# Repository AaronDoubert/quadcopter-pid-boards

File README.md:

# Quadcopter Flight Controller – Analog PID Boards

Analog PID flight controller for a 5" quadcopter: roll, pitch and yaw loops built from op-amps and
trimpots, fed by an MPU-6050 through a small ATtiny/DAC "shim", driving a 4in1 ESC. Designed in KiCad 10.

## PID_Board rev B: compact through-hole board for the 5" frame (latest)

**90 x 210 mm, 4-layer, all through-hole except the two SOIC ATtinys.** It mounts straight onto the frame.

| | |
|---|---|
| Mounting | 30.5 x 30.5 stack holes + 20 x 20 ESC stack holes (M3); copper-free rings for the standoffs |
| ESC | 4in1 sits underneath the rear section on the 20x20 holes; harness to J5 |
| IMU | GY-521 on a header, MPU-6050 directly over the frame CG |
| Receiver | ELRS 2.4 GHz (for example RadioMaster RP1/RP2), CRSF on J6 at the front edge |
| Power | VBAT (2S–4S) from the ESC harness → 1N5817 → mini fixed-5 V buck module on U10 (3 wires; see MOUNTING.md) |
| Tuning | One labelled panel per axis: test points, LOOP/GYRO jumpers, Go/Kp/Ki/Kd trimpots, all prop-clear |
| Layers | Top/bottom signals, In1 GND plane, In2 +5 V plane |

<table>
<tr>
<td></td>
<td></td>
<td></td>
</tr>
<tr><td>Board on the frame (dashed: 5" prop disks)</td><td>Top</td><td>Bottom</td></tr>
</table>

**Order / build files**
- **Gerbers (upload this zip to JLCPCB or PCBWay as a 4-layer board):** [`PID_Board_gerbers_drill.zip`](PID_Board/fab/JLC_PCBWay_THT/PID_Board_gerbers_drill.zip)
- **BOM and pick-and-place:** [`PID_Board/fab/JLC_PCBWay_THT/`](PID_Board/fab/JLC_PCBWay_THT/) (grouped BOM, CPL)
- **3D model:** [`PID_Board/cad/`](PID_Board/cad/) (STEP).
- [`PID_Board/MOUNTING.md`](PID_Board/MOUNTING.md): stack order, standoffs, where each module goes, what to measure before ordering.
- [`PID_Board/KNOWN_ISSUES.md`](PID_Board/KNOWN_ISSUES.md): things to check before first power-up.

## PID_Board_SMT: SMT, digital-pot version

100 x 100 mm 2-layer, assembly-ready at JLCPCB (LCSC part numbers), digital pots instead of trimpots.

Files: `PID_Board_SMT/fab/` (Gerbers, BOM, CPL), `PID_Board_SMT/SMT_NOTES.md`, `PID_Board_SMT/scripts/`.

## Simulation: quad model + digital twin of the board

[`sim/`](sim/README.md) holds two linked Simulink models (R2024b):
- **The quad:** 6-DOF 5" quad with 2207 1800KV motors, 5x4.3x3 props, a 4S battery with voltage sag, the ESC and the MPU-6050.
- **The board twin:** shim, all 5 analog loops, control_io. The analog section comes as either a fast behavioural model or a Simscape Electrical circuit model.

The board twin plugs into the quad's controller slot, or runs on a bench harness that mirrors the real board's test points.

**[First-flight trimpot settings](sim/gains/first_flight_gains.md)** are conservative values checked in the sim, with margin for inertia and delay errors. How they were chosen and a suggested first-flight procedure are in [`sim/gains/README.md`](sim/gains/README.md).

## Repository layout
| Path | What |
|---|---|
| `PID_Board/` | Through-hole board, rev B (current) |
| `PID_Board/old_versions/` | Earlier through-hole revisions (v1, rev A: 250 x 100 mm bench layout) |
| `PID_Board_SMT/` | SMT / digital-pot board |
| [`sim/`](sim/README.md) | Simulink quad model, board twin (fast + Simscape circuit), first-flight gains, docs |
| [`CHANGELOG.md`](CHANGELOG.md) | Version history |

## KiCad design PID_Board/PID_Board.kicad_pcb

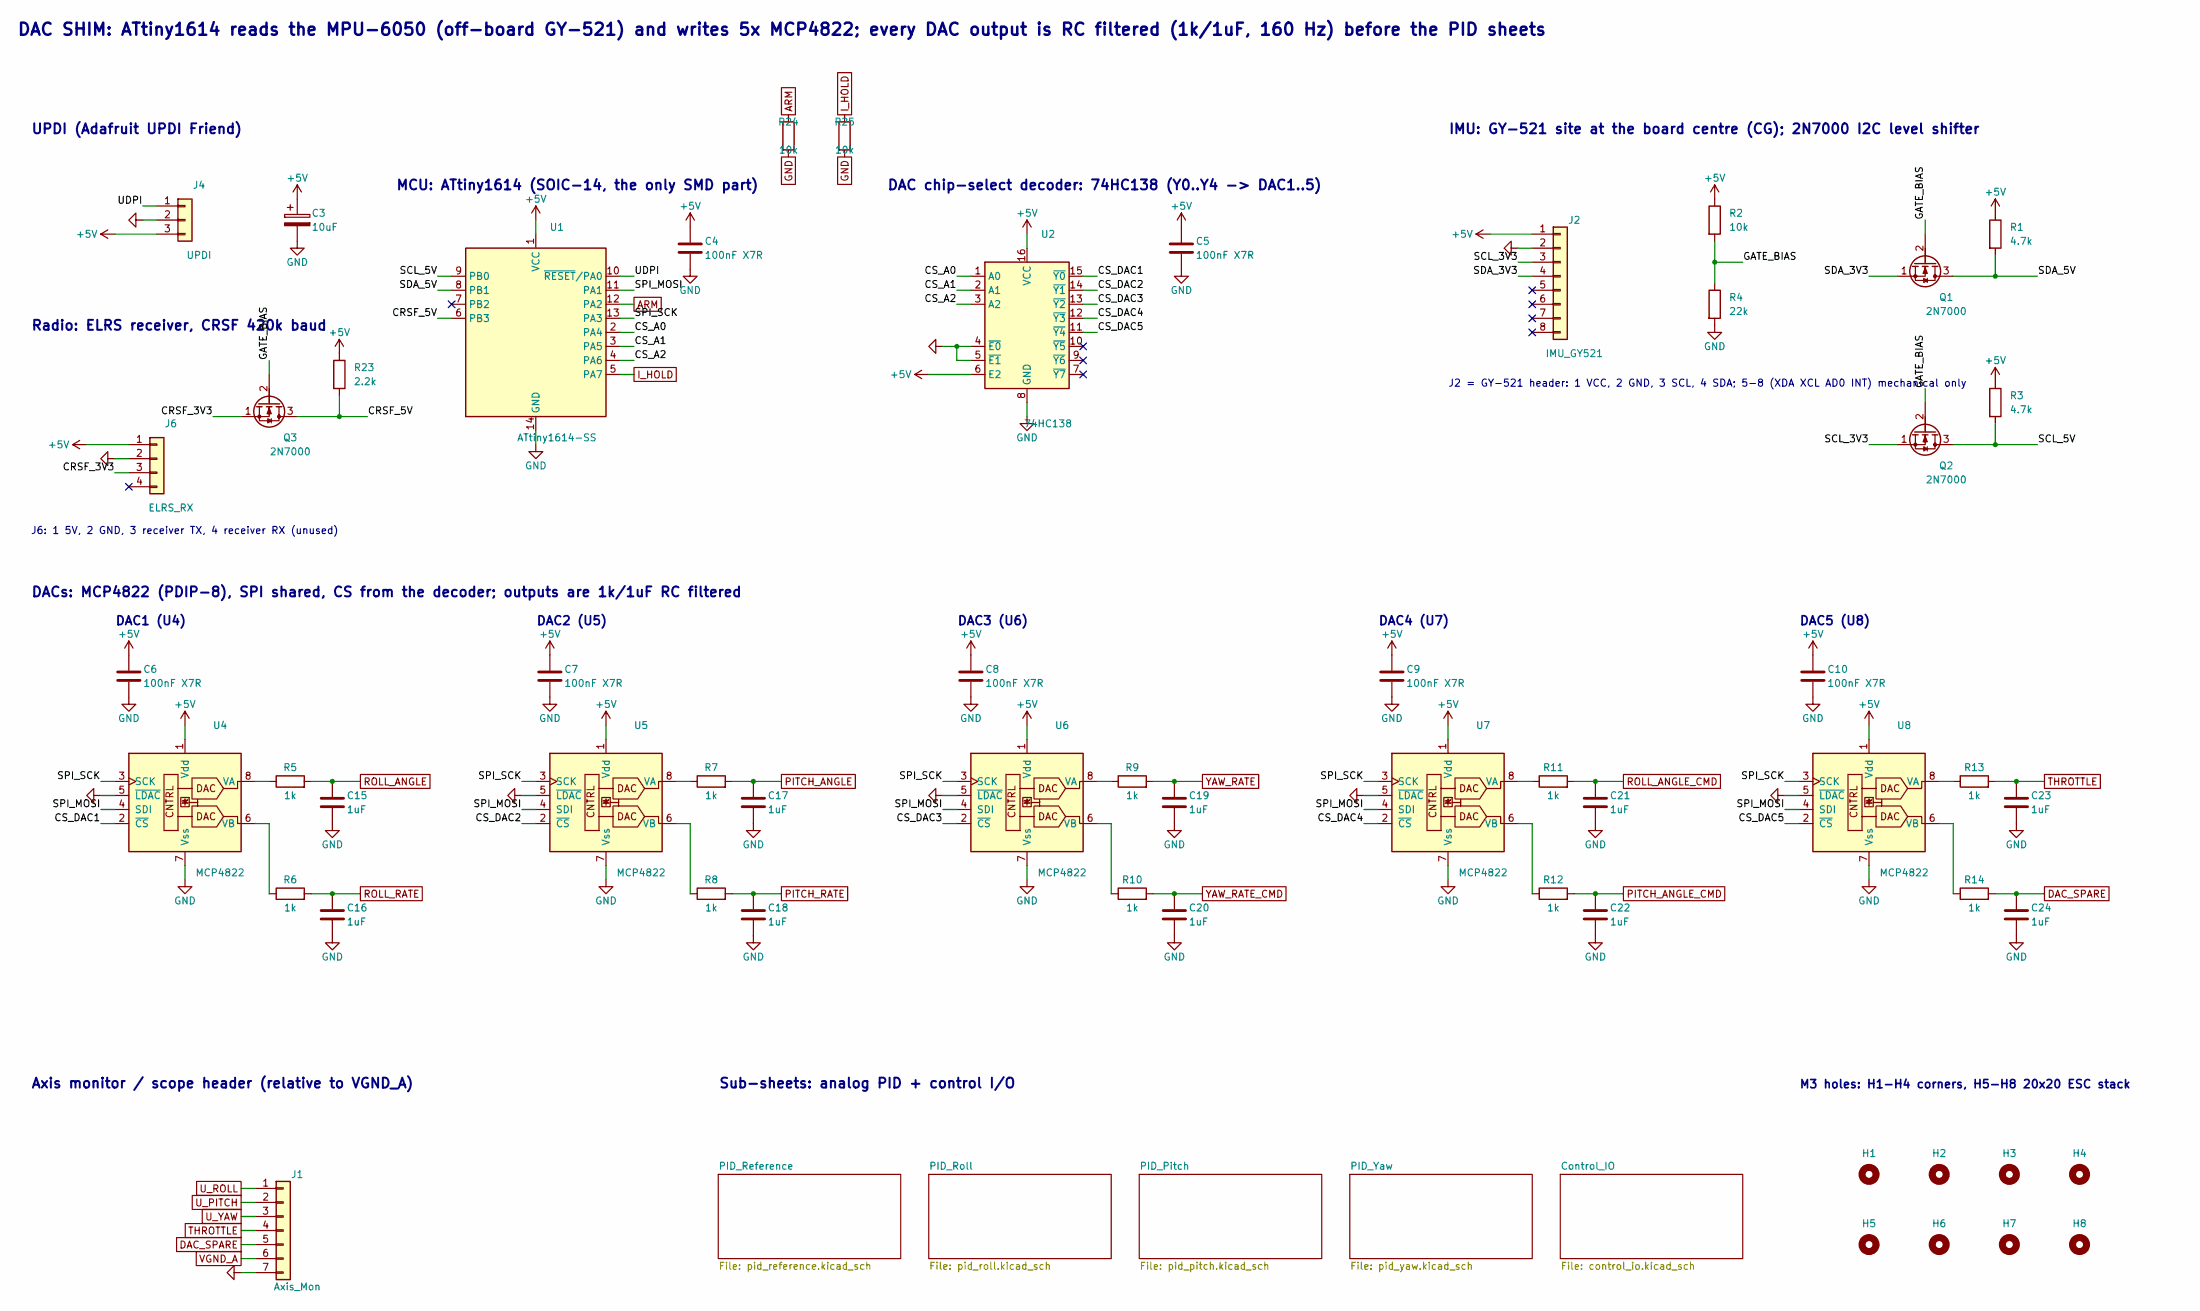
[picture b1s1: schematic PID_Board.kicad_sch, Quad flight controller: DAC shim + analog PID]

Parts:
C3: 10uF; CP_Radial_D5.0mm_P2.00mm
C4, C5, C6, C7, C8, C9, C10: 100nF X7R; C_Disc_D5.0mm_W2.5mm_P5.00mm
C15, C16, C17, C18, C19, C20, C21, C22, C23, C24: 1uF; C_Disc_D5.0mm_W2.5mm_P5.00mm
H1, H2, H3, H4, H5, H6, H7, H8: MountingHole; MountingHole_3.2mm_M3
J1: Axis_Mon; PinHeader_1x07_P2.54mm_Vertical
J2: IMU_GY521; PinHeader_1x08_P2.54mm_Vertical
J4: UPDI; PinHeader_1x03_P2.54mm_Vertical
J6: ELRS_RX; PinHeader_1x04_P2.54mm_Vertical
Q1, Q2, Q3: 2N7000; TO-92_Inline_Wide
R1, R3: 4.7k; R_Axial_DIN0207_L6.3mm_D2.5mm_P7.62mm_Horizontal
R2, R24, R25: 10k; R_Axial_DIN0207_L6.3mm_D2.5mm_P7.62mm_Horizontal
R4: 22k; R_Axial_DIN0207_L6.3mm_D2.5mm_P7.62mm_Horizontal
R5, R6, R7, R8, R9, R10, R11, R12, R13, R14: 1k; R_Axial_DIN0207_L6.3mm_D2.5mm_P7.62mm_Horizontal
R23: 2.2k; R_Axial_DIN0207_L6.3mm_D2.5mm_P7.62mm_Horizontal
U1: ATtiny1614-SS; SOIC-14_3.9x8.7mm_P1.27mm
U2: 74HC138; DIP-16_W7.62mm
U4, U5, U6, U7, U8: MCP4822; DIP-8_W7.62mm

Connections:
+5V: C3.1, C4.1, C5.1, C6.1, C7.1, C8.1, C9.1, C10.1, J2.1, J4.3, J6.1, R1.1, R2.1, R3.1, R23.1, U1.1 (VCC), U2.6 (E2), U2.16 (VCC), U4.1 (Vdd), U5.1 (Vdd), U6.1 (Vdd), U7.1 (Vdd), U8.1 (Vdd); also elsewhere on the board
/CRSF_3V3: J6.3, Q3.1 (S)
/CRSF_5V: Q3.3 (D), R23.2, U1.6 (PB3)
/CS_A0: U1.2 (PA4), U2.1 (A0)
/CS_A1: U1.3 (PA5), U2.2 (A1)
/CS_A2: U1.4 (PA6), U2.3 (A2)
/CS_DAC1: U2.15 (~Y0), U4.2 (~CS)
/CS_DAC2: U2.14 (~Y1), U5.2 (~CS)
/CS_DAC3: U2.13 (~Y2), U6.2 (~CS)
/CS_DAC4: U2.12 (~Y3), U7.2 (~CS)
/CS_DAC5: U2.11 (~Y4), U8.2 (~CS)
/GATE_BIAS: Q1.2 (G), Q2.2 (G), Q3.2 (G), R2.2, R4.1
/SCL_3V3: J2.3, Q2.1 (S)
/SCL_5V: Q2.3 (D), R3.2, U1.9 (PB0)
/SDA_3V3: J2.4, Q1.1 (S)
/SDA_5V: Q1.3 (D), R1.2, U1.8 (PB1)
/SPI_MOSI: U1.11 (PA1), U4.4 (SDI), U5.4 (SDI), U6.4 (SDI), U7.4 (SDI), U8.4 (SDI)
/SPI_SCK: U1.13 (PA3), U4.3 (SCK), U5.3 (SCK), U6.3 (SCK), U7.3 (SCK), U8.3 (SCK)
/UDPI: J4.1, U1.10 (~RESET/PA0)
ARM: R24.1, U1.12 (PA2); also elsewhere on the board
DAC_SPARE: C24.1, J1.5, R14.2
GND: C3.2, C4.2, C5.2, C6.2, C7.2, C8.2, C9.2, C10.2, C15.2, C16.2, C17.2, C18.2, C19.2, C20.2, C21.2, C22.2, C23.2, C24.2, J1.7, J2.2, J4.2, J6.2, R4.2, R24.2, R25.2, U1.14 (GND), U2.4 (~E0), U2.5 (~E1), U2.8 (GND), U4.5 (~LDAC), U4.7 (Vss), U5.5 (~LDAC), U5.7 (Vss), U6.5 (~LDAC), U6.7 (Vss), U7.5 (~LDAC), U7.7 (Vss), U8.5 (~LDAC), U8.7 (Vss); also elsewhere on the board
I_HOLD: R25.1, U1.5 (PA7); also elsewhere on the board
unnamed: R5.1, U4.8 (VA)
unnamed: R6.1, U4.6 (VB)
unnamed: R7.1, U5.8 (VA)
unnamed: R8.1, U5.6 (VB)
unnamed: R9.1, U6.8 (VA)
unnamed: R10.1, U6.6 (VB)
unnamed: R11.1, U7.8 (VA)
unnamed: R12.1, U7.6 (VB)
unnamed: R13.1, U8.8 (VA)
unnamed: R14.1, U8.6 (VB)
PITCH_ANGLE: C17.1, R7.2; also elsewhere on the board
PITCH_ANGLE_CMD: C22.1, R12.2; also elsewhere on the board
PITCH_RATE: C18.1, R8.2; also elsewhere on the board
ROLL_ANGLE: C15.1, R5.2; also elsewhere on the board
ROLL_ANGLE_CMD: C21.1, R11.2; also elsewhere on the board
ROLL_RATE: C16.1, R6.2; also elsewhere on the board
THROTTLE: C23.1, J1.4, R13.2; also elsewhere on the board
U_PITCH: J1.2; also elsewhere on the board
U_ROLL: J1.1; also elsewhere on the board
U_YAW: J1.3; also elsewhere on the board
VGND_A: J1.6; also elsewhere on the board
YAW_RATE: C19.1, R9.2; also elsewhere on the board
YAW_RATE_CMD: C20.1, R10.2; also elsewhere on the board

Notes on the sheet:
DAC SHIM: ATtiny1614 reads the MPU-6050 (off-board GY-521) and writes 5x MCP4822; every DAC output is RC filtered (1k/1uF, 160 Hz) before the PID sheets
UPDI (Adafruit UPDI Friend)
Radio: ELRS receiver, CRSF 420k baud
J6: 1 5V, 2 GND, 3 receiver TX, 4 receiver RX (unused)
MCU: ATtiny1614 (SOIC-14, the only SMD part)
DAC chip-select decoder: 74HC138 (Y0..Y4 -> DAC1..5)
IMU: GY-521 site at the board centre (CG); 2N7000 I2C level shifter
J2 = GY-521 header: 1 VCC, 2 GND, 3 SCL, 4 SDA; 5-8 (XDA XCL AD0 INT) mechanical only
DACs: MCP4822 (PDIP-8), SPI shared, CS from the decoder; outputs are 1k/1uF RC filtered
DAC1 (U4)
DAC2 (U5)
DAC3 (U6)
DAC4 (U7)
DAC5 (U8)
Axis monitor / scope header (relative to VGND_A)
M3 holes: H1-H4 corners, H5-H8 20x20 ESC stack
Sub-sheets: analog PID + control I/O

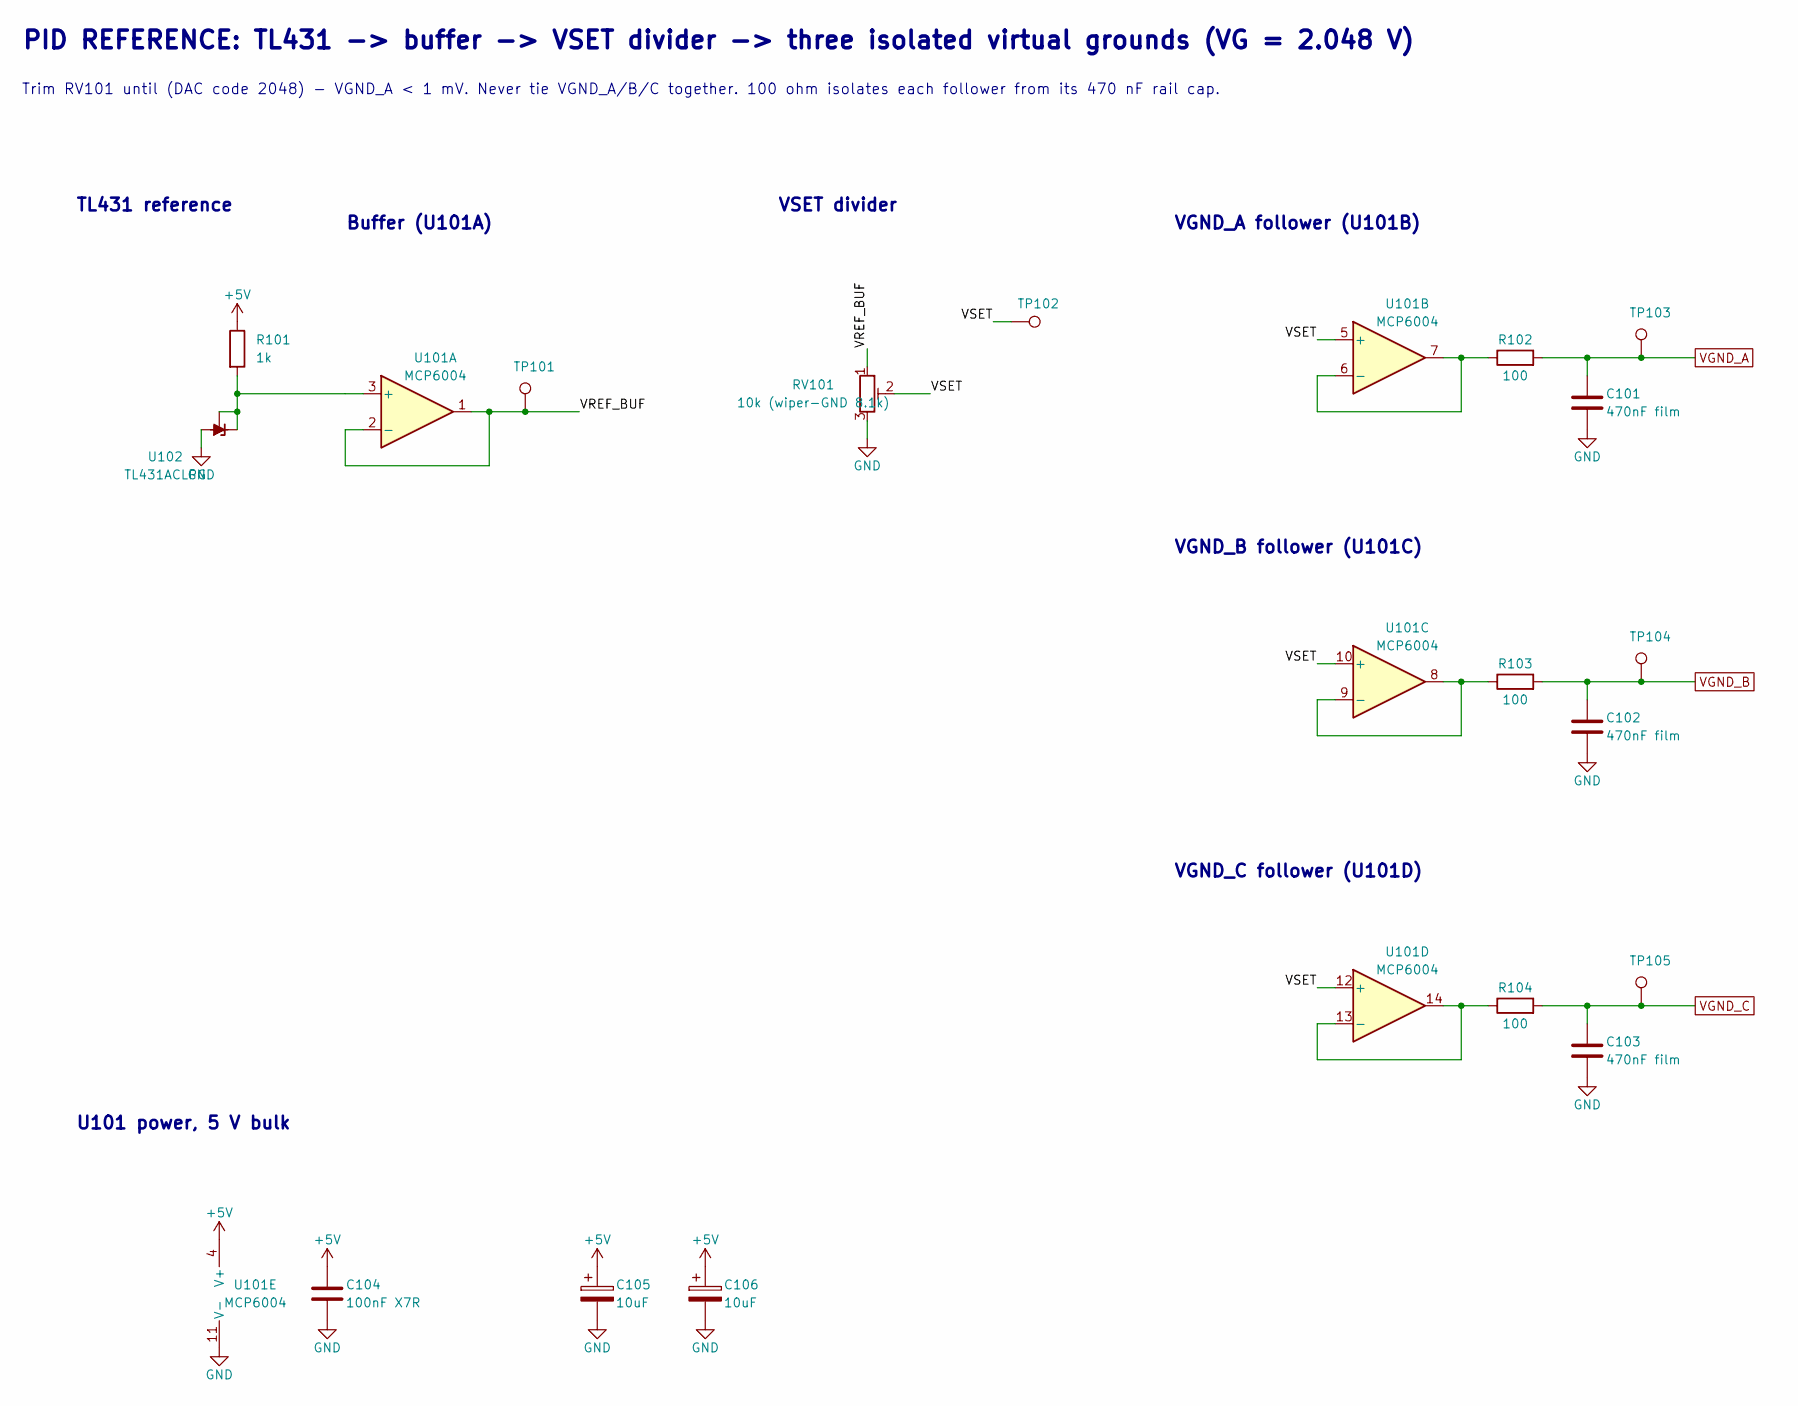
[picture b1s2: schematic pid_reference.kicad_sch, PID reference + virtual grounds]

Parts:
C101, C102, C103: 470nF film; C_Rect_L7.2mm_W4.5mm_P5.00mm_FKS2_FKP2_MKS2_MKP2
C104: 100nF X7R; C_Disc_D5.0mm_W2.5mm_P5.00mm
C105, C106: 10uF; CP_Radial_D5.0mm_P2.00mm
R101: 1k; R_Axial_DIN0207_L6.3mm_D2.5mm_P7.62mm_Horizontal
R102, R103, R104: 100; R_Axial_DIN0207_L6.3mm_D2.5mm_P7.62mm_Horizontal
RV101: 10k (wiper-GND 8.1k); Potentiometer_Bourns_3296W_Vertical
TP101: VREF_BUF; PinHeader_1x01_P2.54mm_Vertical
TP102: VSET; PinHeader_1x01_P2.54mm_Vertical
TP103: VGND_A; PinHeader_1x01_P2.54mm_Vertical
TP104: VGND_B; PinHeader_1x01_P2.54mm_Vertical
TP105: VGND_C; PinHeader_1x01_P2.54mm_Vertical
U101: MCP6004; DIP-14_W7.62mm
U102: TL431ACLPG; TO-92_Inline_Wide

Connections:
+5V: C104.1, C105.1, C106.1, R101.1, U101.4 (V+); also elsewhere on the board
/PID_Reference/VREF_BUF: RV101.1, TP101.1, U101.1, U101.2 (-)
/PID_Reference/VSET: RV101.2, TP102.1, U101.5 (+), U101.10 (+), U101.12 (+)
GND: C101.2, C102.2, C103.2, C104.2, C105.2, C106.2, RV101.3, U101.11 (V-), U102.2 (A); also elsewhere on the board
unnamed: R101.2, U101.3 (+), U102.1 (REF), U102.3 (K)
unnamed: R102.1, U101.6 (-), U101.7
unnamed: R103.1, U101.8, U101.9 (-)
unnamed: R104.1, U101.13 (-), U101.14
VGND_A: C101.1, R102.2, TP103.1; also elsewhere on the board
VGND_B: C102.1, R103.2, TP104.1; also elsewhere on the board
VGND_C: C103.1, R104.2, TP105.1; also elsewhere on the board

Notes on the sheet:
PID REFERENCE: TL431 -> buffer -> VSET divider -> three isolated virtual grounds (VG = 2.048 V)
Trim RV101 until (DAC code 2048) - VGND_A < 1 mV. Never tie VGND_A/B/C together. 100 ohm isolates each follower from its 470 nF rail cap.
TL431 reference
Buffer (U101A)
VSET divider
VGND_A follower (U101B)
VGND_B follower (U101C)
VGND_C follower (U101D)
U101 power, 5 V bulk

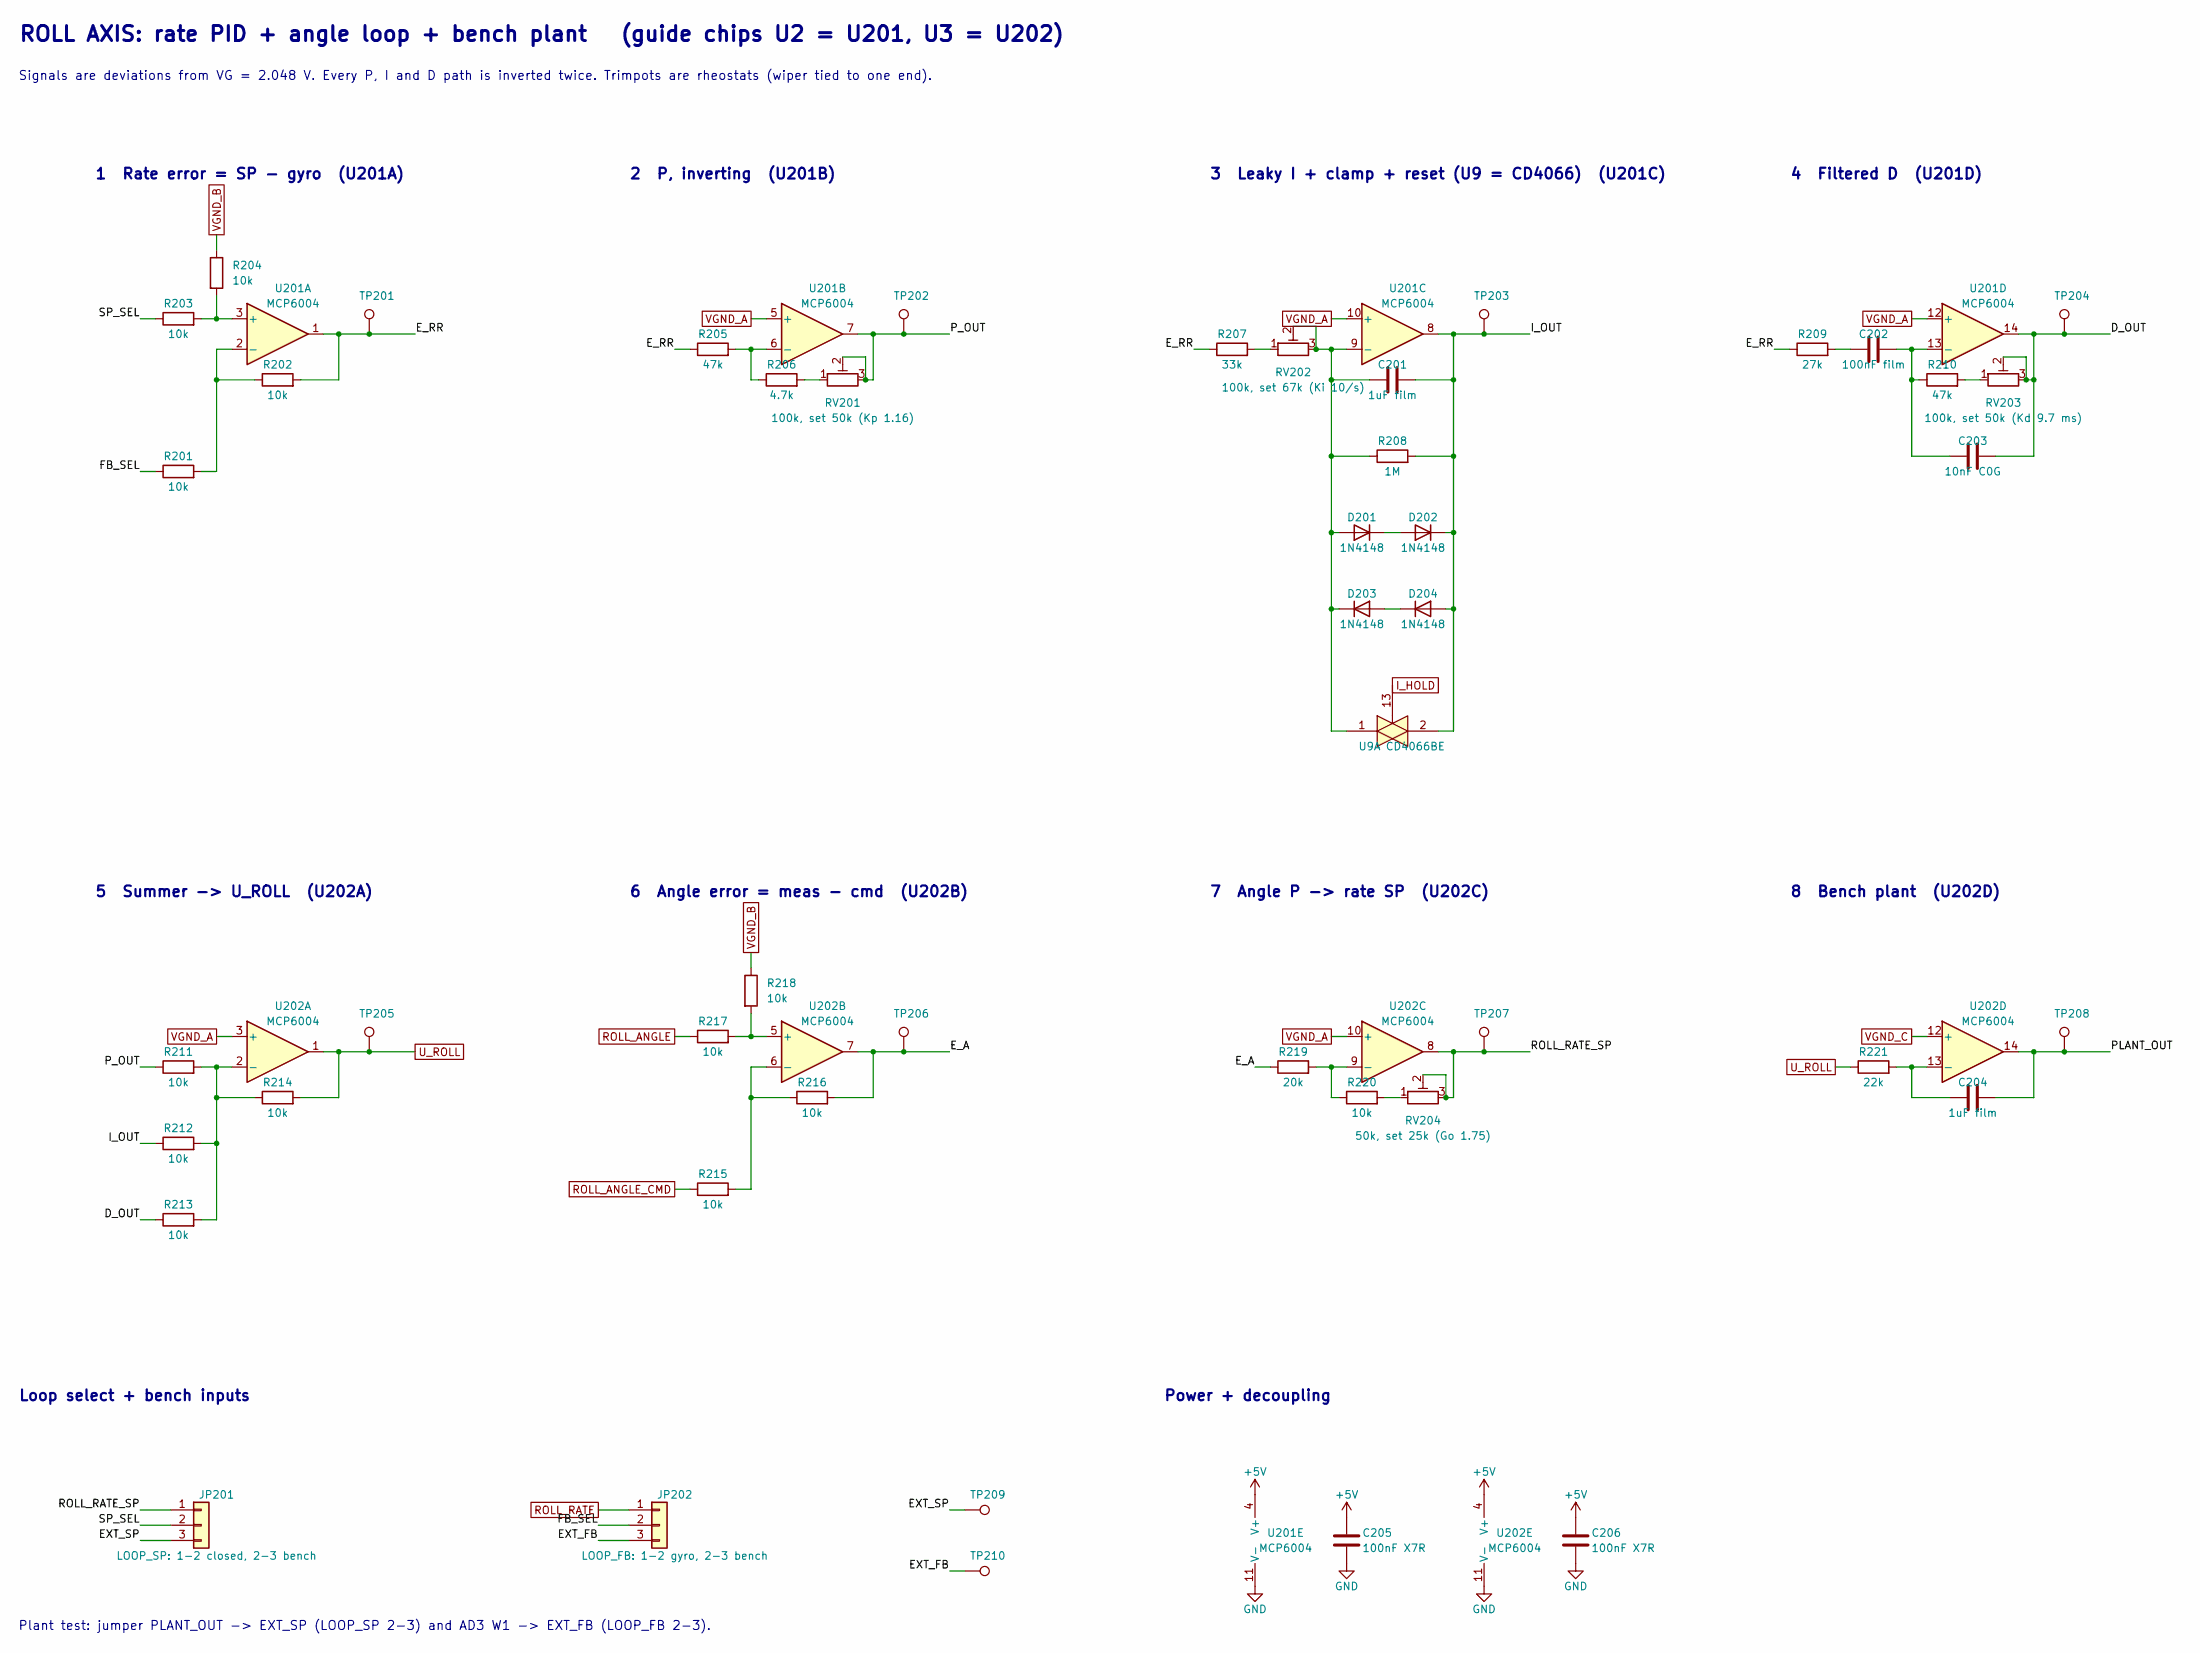
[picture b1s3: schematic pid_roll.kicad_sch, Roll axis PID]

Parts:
C201, C204: 1uF film; C_Rect_L7.2mm_W5.5mm_P5.00mm_FKS2_FKP2_MKS2_MKP2
C202: 100nF film; C_Rect_L7.2mm_W2.5mm_P5.00mm_FKS2_FKP2_MKS2_MKP2
C203: 10nF C0G; C_Disc_D5.0mm_W2.5mm_P5.00mm
C205, C206: 100nF X7R; C_Disc_D5.0mm_W2.5mm_P5.00mm
D201, D202, D203, D204: 1N4148; D_DO-35_SOD27_P7.62mm_Horizontal
JP201: LOOP_SP: 1-2 closed, 2-3 bench; PinHeader_1x03_P2.54mm_Vertical
JP202: LOOP_FB: 1-2 gyro, 2-3 bench; PinHeader_1x03_P2.54mm_Vertical
R201, R202, R203, R204, R211, R212, R213, R214, R215, R216, R217, R218, R220: 10k; R_Axial_DIN0207_L6.3mm_D2.5mm_P7.62mm_Horizontal
R205, R210: 47k; R_Axial_DIN0207_L6.3mm_D2.5mm_P7.62mm_Horizontal
R206: 4.7k; R_Axial_DIN0207_L6.3mm_D2.5mm_P7.62mm_Horizontal
R207: 33k; R_Axial_DIN0207_L6.3mm_D2.5mm_P7.62mm_Horizontal
R208: 1M; R_Axial_DIN0207_L6.3mm_D2.5mm_P7.62mm_Horizontal
R209: 27k; R_Axial_DIN0207_L6.3mm_D2.5mm_P7.62mm_Horizontal
R219: 20k; R_Axial_DIN0207_L6.3mm_D2.5mm_P7.62mm_Horizontal
R221: 22k; R_Axial_DIN0207_L6.3mm_D2.5mm_P7.62mm_Horizontal
RV201: 100k, set 50k (Kp 1.16); Potentiometer_Bourns_3296W_Vertical
RV202: 100k, set 67k (Ki 10/s); Potentiometer_Bourns_3296W_Vertical
RV203: 100k, set 50k (Kd 9.7 ms); Potentiometer_Bourns_3296W_Vertical
RV204: 50k, set 25k (Go 1.75); Potentiometer_Bourns_3296W_Vertical
TP201: E_RR; PinHeader_1x01_P2.54mm_Vertical
TP202: P_OUT; PinHeader_1x01_P2.54mm_Vertical
TP203: I_OUT; PinHeader_1x01_P2.54mm_Vertical
TP204: D_OUT; PinHeader_1x01_P2.54mm_Vertical
TP205: U_ROLL; PinHeader_1x01_P2.54mm_Vertical
TP206: E_A; PinHeader_1x01_P2.54mm_Vertical
TP207: ROLL_RATE_SP; PinHeader_1x01_P2.54mm_Vertical
TP208: PLANT_OUT; PinHeader_1x01_P2.54mm_Vertical
TP209: EXT_SP; PinHeader_1x01_P2.54mm_Vertical
TP210: EXT_FB; PinHeader_1x01_P2.54mm_Vertical
U9: CD4066BE; DIP-14_W7.62mm
U201, U202: MCP6004; DIP-14_W7.62mm

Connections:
+5V: C205.1, C206.1, U201.4 (V+), U202.4 (V+); also elsewhere on the board
/PID_Roll/D_OUT: C203.2, R213.1, RV203.2, RV203.3, TP204.1, U201.14
/PID_Roll/EXT_FB: JP202.3, TP210.1
/PID_Roll/EXT_SP: JP201.3, TP209.1
/PID_Roll/E_A: R216.2, R219.1, TP206.1, U202.7
/PID_Roll/E_RR: R202.2, R205.1, R207.1, R209.1, TP201.1, U201.1
/PID_Roll/FB_SEL: JP202.2, R201.1
/PID_Roll/I_OUT: C201.2, D202.1 (K), D204.2 (A), R208.2, R212.1, TP203.1, U9.2, U201.8
/PID_Roll/PLANT_OUT: C204.2, TP208.1, U202.14
/PID_Roll/P_OUT: R211.1, RV201.2, RV201.3, TP202.1, U201.7
/PID_Roll/ROLL_RATE_SP: JP201.1, RV204.2, RV204.3, TP207.1, U202.8
/PID_Roll/SP_SEL: JP201.2, R203.1
GND: C205.2, C206.2, U201.11 (V-), U202.11 (V-); also elsewhere on the board
I_HOLD: U9.13; also elsewhere on the board
unnamed: C202.1, R209.2
unnamed: C201.1, D201.2 (A), D203.1 (K), R208.1, RV202.2, RV202.3, U9.1, U201.9 (-)
unnamed: D201.1 (K), D202.2 (A)
unnamed: D203.2 (A), D204.1 (K)
unnamed: R206.2, RV201.1
unnamed: R207.2, RV202.1
unnamed: R210.2, RV203.1
unnamed: R220.2, RV204.1
unnamed: R203.2, R204.2, U201.3 (+)
unnamed: R201.2, R202.1, U201.2 (-)
unnamed: R205.2, R206.1, U201.6 (-)
unnamed: C202.2, C203.1, R210.1, U201.13 (-)
unnamed: R211.2, R212.2, R213.2, R214.1, U202.2 (-)
unnamed: R217.2, R218.2, U202.5 (+)
unnamed: R215.2, R216.1, U202.6 (-)
unnamed: R219.2, R220.1, U202.9 (-)
unnamed: C204.1, R221.2, U202.13 (-)
ROLL_ANGLE: R217.1; also elsewhere on the board
ROLL_ANGLE_CMD: R215.1; also elsewhere on the board
ROLL_RATE: JP202.1; also elsewhere on the board
U_ROLL: R214.2, R221.1, TP205.1, U202.1; also elsewhere on the board
VGND_A: U201.5 (+), U201.10 (+), U201.12 (+), U202.3 (+), U202.10 (+); also elsewhere on the board
VGND_B: R204.1, R218.1; also elsewhere on the board
VGND_C: U202.12 (+); also elsewhere on the board

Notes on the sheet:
ROLL AXIS: rate PID + angle loop + bench plant (guide chips U2 = U201, U3 = U202)
Signals are deviations from VG = 2.048 V. Every P, I and D path is inverted twice. Trimpots are rheostats (wiper tied to one end).
1 Rate error = SP - gyro (U201A)
2 P, inverting (U201B)
3 Leaky I + clamp + reset (U9 = CD4066) (U201C)
4 Filtered D (U201D)
5 Summer -> U_ROLL (U202A)
6 Angle error = meas - cmd (U202B)
7 Angle P -> rate SP (U202C)
8 Bench plant (U202D)
Loop select + bench inputs
Plant test: jumper PLANT_OUT -> EXT_SP (LOOP_SP 2-3) and AD3 W1 -> EXT_FB (LOOP_FB 2-3).
Power + decoupling

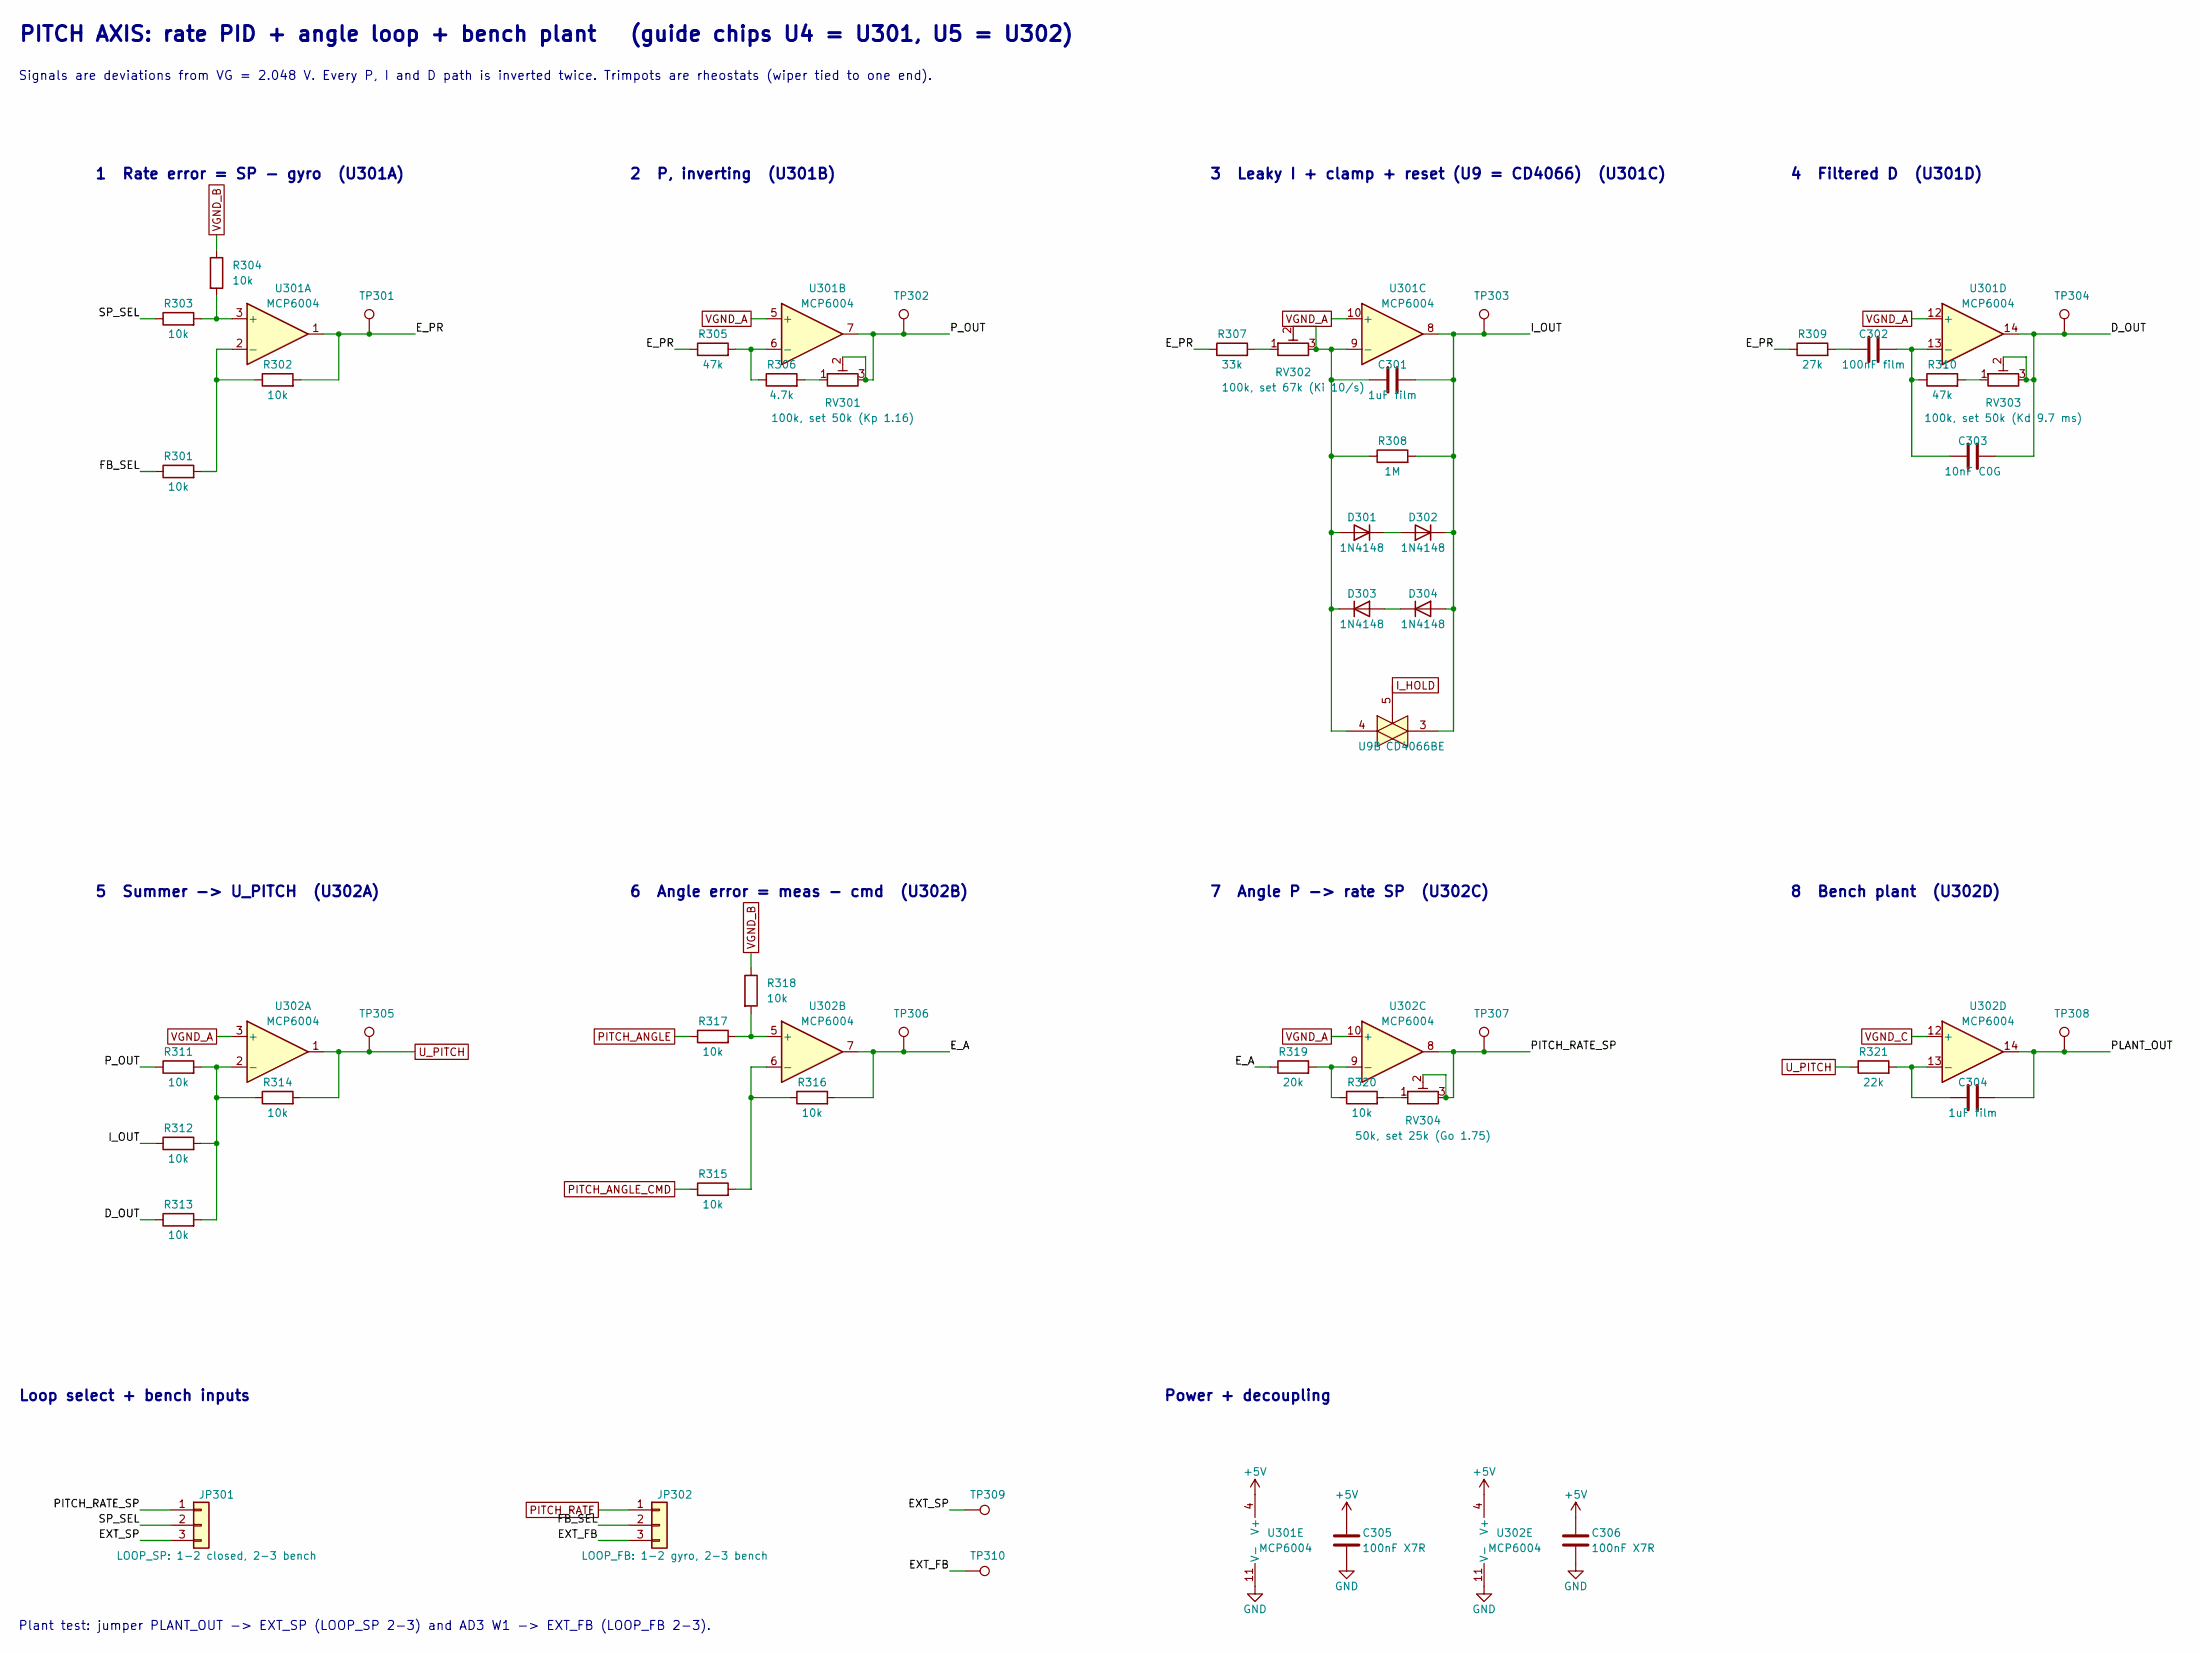
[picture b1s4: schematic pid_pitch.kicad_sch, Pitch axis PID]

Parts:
C301, C304: 1uF film; C_Rect_L7.2mm_W5.5mm_P5.00mm_FKS2_FKP2_MKS2_MKP2
C302: 100nF film; C_Rect_L7.2mm_W2.5mm_P5.00mm_FKS2_FKP2_MKS2_MKP2
C303: 10nF C0G; C_Disc_D5.0mm_W2.5mm_P5.00mm
C305, C306: 100nF X7R; C_Disc_D5.0mm_W2.5mm_P5.00mm
D301, D302, D303, D304: 1N4148; D_DO-35_SOD27_P7.62mm_Horizontal
JP301: LOOP_SP: 1-2 closed, 2-3 bench; PinHeader_1x03_P2.54mm_Vertical
JP302: LOOP_FB: 1-2 gyro, 2-3 bench; PinHeader_1x03_P2.54mm_Vertical
R301, R302, R303, R304, R311, R312, R313, R314, R315, R316, R317, R318, R320: 10k; R_Axial_DIN0207_L6.3mm_D2.5mm_P7.62mm_Horizontal
R305, R310: 47k; R_Axial_DIN0207_L6.3mm_D2.5mm_P7.62mm_Horizontal
R306: 4.7k; R_Axial_DIN0207_L6.3mm_D2.5mm_P7.62mm_Horizontal
R307: 33k; R_Axial_DIN0207_L6.3mm_D2.5mm_P7.62mm_Horizontal
R308: 1M; R_Axial_DIN0207_L6.3mm_D2.5mm_P7.62mm_Horizontal
R309: 27k; R_Axial_DIN0207_L6.3mm_D2.5mm_P7.62mm_Horizontal
R319: 20k; R_Axial_DIN0207_L6.3mm_D2.5mm_P7.62mm_Horizontal
R321: 22k; R_Axial_DIN0207_L6.3mm_D2.5mm_P7.62mm_Horizontal
RV301: 100k, set 50k (Kp 1.16); Potentiometer_Bourns_3296W_Vertical
RV302: 100k, set 67k (Ki 10/s); Potentiometer_Bourns_3296W_Vertical
RV303: 100k, set 50k (Kd 9.7 ms); Potentiometer_Bourns_3296W_Vertical
RV304: 50k, set 25k (Go 1.75); Potentiometer_Bourns_3296W_Vertical
TP301: E_PR; PinHeader_1x01_P2.54mm_Vertical
TP302: P_OUT; PinHeader_1x01_P2.54mm_Vertical
TP303: I_OUT; PinHeader_1x01_P2.54mm_Vertical
TP304: D_OUT; PinHeader_1x01_P2.54mm_Vertical
TP305: U_PITCH; PinHeader_1x01_P2.54mm_Vertical
TP306: E_A; PinHeader_1x01_P2.54mm_Vertical
TP307: PITCH_RATE_SP; PinHeader_1x01_P2.54mm_Vertical
TP308: PLANT_OUT; PinHeader_1x01_P2.54mm_Vertical
TP309: EXT_SP; PinHeader_1x01_P2.54mm_Vertical
TP310: EXT_FB; PinHeader_1x01_P2.54mm_Vertical
U9: CD4066BE; DIP-14_W7.62mm
U301, U302: MCP6004; DIP-14_W7.62mm

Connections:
+5V: C305.1, C306.1, U301.4 (V+), U302.4 (V+); also elsewhere on the board
/PID_Pitch/D_OUT: C303.2, R313.1, RV303.2, RV303.3, TP304.1, U301.14
/PID_Pitch/EXT_FB: JP302.3, TP310.1
/PID_Pitch/EXT_SP: JP301.3, TP309.1
/PID_Pitch/E_A: R316.2, R319.1, TP306.1, U302.7
/PID_Pitch/E_PR: R302.2, R305.1, R307.1, R309.1, TP301.1, U301.1
/PID_Pitch/FB_SEL: JP302.2, R301.1
/PID_Pitch/I_OUT: C301.2, D302.1 (K), D304.2 (A), R308.2, R312.1, TP303.1, U9.3, U301.8
/PID_Pitch/PITCH_RATE_SP: JP301.1, RV304.2, RV304.3, TP307.1, U302.8
/PID_Pitch/PLANT_OUT: C304.2, TP308.1, U302.14
/PID_Pitch/P_OUT: R311.1, RV301.2, RV301.3, TP302.1, U301.7
/PID_Pitch/SP_SEL: JP301.2, R303.1
GND: C305.2, C306.2, U301.11 (V-), U302.11 (V-); also elsewhere on the board
I_HOLD: U9.5; also elsewhere on the board
unnamed: C302.1, R309.2
unnamed: C301.1, D301.2 (A), D303.1 (K), R308.1, RV302.2, RV302.3, U9.4, U301.9 (-)
unnamed: D301.1 (K), D302.2 (A)
unnamed: D303.2 (A), D304.1 (K)
unnamed: R306.2, RV301.1
unnamed: R307.2, RV302.1
unnamed: R310.2, RV303.1
unnamed: R320.2, RV304.1
unnamed: R303.2, R304.2, U301.3 (+)
unnamed: R301.2, R302.1, U301.2 (-)
unnamed: R305.2, R306.1, U301.6 (-)
unnamed: C302.2, C303.1, R310.1, U301.13 (-)
unnamed: R311.2, R312.2, R313.2, R314.1, U302.2 (-)
unnamed: R317.2, R318.2, U302.5 (+)
unnamed: R315.2, R316.1, U302.6 (-)
unnamed: R319.2, R320.1, U302.9 (-)
unnamed: C304.1, R321.2, U302.13 (-)
PITCH_ANGLE: R317.1; also elsewhere on the board
PITCH_ANGLE_CMD: R315.1; also elsewhere on the board
PITCH_RATE: JP302.1; also elsewhere on the board
U_PITCH: R314.2, R321.1, TP305.1, U302.1; also elsewhere on the board
VGND_A: U301.5 (+), U301.10 (+), U301.12 (+), U302.3 (+), U302.10 (+); also elsewhere on the board
VGND_B: R304.1, R318.1; also elsewhere on the board
VGND_C: U302.12 (+); also elsewhere on the board

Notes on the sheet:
PITCH AXIS: rate PID + angle loop + bench plant (guide chips U4 = U301, U5 = U302)
Signals are deviations from VG = 2.048 V. Every P, I and D path is inverted twice. Trimpots are rheostats (wiper tied to one end).
1 Rate error = SP - gyro (U301A)
2 P, inverting (U301B)
3 Leaky I + clamp + reset (U9 = CD4066) (U301C)
4 Filtered D (U301D)
5 Summer -> U_PITCH (U302A)
6 Angle error = meas - cmd (U302B)
7 Angle P -> rate SP (U302C)
8 Bench plant (U302D)
Loop select + bench inputs
Plant test: jumper PLANT_OUT -> EXT_SP (LOOP_SP 2-3) and AD3 W1 -> EXT_FB (LOOP_FB 2-3).
Power + decoupling
